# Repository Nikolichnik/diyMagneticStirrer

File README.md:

# diyMagneticStirrer
Simple laboratory magnetic stirrer.

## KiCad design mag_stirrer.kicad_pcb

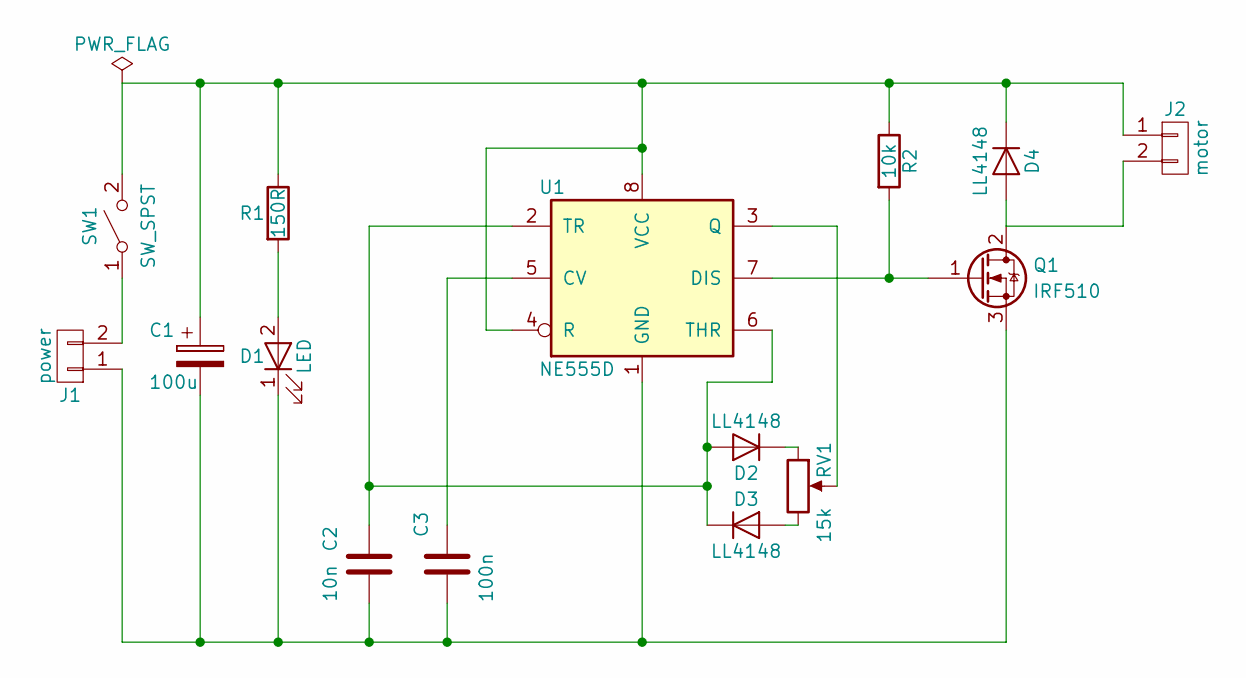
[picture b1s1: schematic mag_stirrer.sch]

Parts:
C1: 100u; CP_Radial_D5.0mm_P2.00mm
C2: 10n; C_0805_HandSoldering
C3: 100n; C_0805_HandSoldering
D1: LED; LED_D5.0mm
D2, D3, D4: LL4148; D_0805
J1: power; Pin_Header_Straight_1x02_Pitch2.00mm
J2: motor; Pin_Header_Straight_1x02_Pitch2.00mm
Q1: IRF510; TO-220
R1: 150R; R_0805
R2: 10k; R_0603
RV1: 15k; Potentiometer_WirePads_Small
SW1: SW_SPST; PINHEAD1-2
U1: NE555D; SOIC-8_3.9x4.9mm_Pitch1.27mm

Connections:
unnamed: C1.1, D4.1 (K), J2.1, R1.1, R2.1, SW1.2 (B), U1.4 (R), U1.8 (VCC)
unnamed: C1.2, C2.1, C3.2, D1.1 (K), J1.1, Q1.3 (S), U1.1 (GND)
unnamed: C2.2, D2.2 (A), D3.1 (K), U1.2 (TR), U1.6 (THR)
unnamed: C3.1, U1.5 (CV)
unnamed: D1.2 (A), R1.2
unnamed: D2.1 (K), RV1.1
unnamed: D3.2 (A), RV1.3
unnamed: D4.2 (A), J2.2, Q1.2 (D)
unnamed: J1.2, SW1.1 (A)
unnamed: Q1.1 (G), R2.2, U1.7 (DIS)
unnamed: RV1.2, U1.3 (Q)

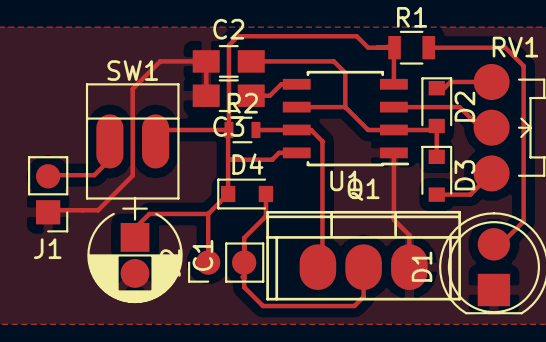
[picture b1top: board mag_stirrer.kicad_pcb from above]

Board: 2 copper layers, 15 parts (0 on the bottom side), 11 nets.
